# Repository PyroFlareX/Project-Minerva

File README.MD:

# Project Minerva

A custom clamshell handheld computer built around the Raspberry Pi Compute Module 5. Minerva combines a gaming-controller form factor with a full Linux environment: dual displays, cellular connectivity, NFC/RFID, and a security-first immutable OS. Every layer of software — compositor, shell, applications — is purpose-built for controller-style interaction.

> **Device:** Minerva &nbsp;|&nbsp; **OS:** Minerva OS &nbsp;|&nbsp; **Desktop Environment:** Torchform

---

## Screenshots & Hardware

| | |
|---|---|
|  |  |
| Torchform shell — home grid, status bar, dock | CM5 carrier board 3D render |
|  |  |
| Work-in-progress PCB layout (KiCad 9) | DSI/CSI display and camera connectors |

---

## What It Is

Minerva is not a game console. It is a general-purpose handheld Linux computer designed for an unconventional input paradigm — no keyboard, no precise pointer. The form factor is a direct reference to the New Nintendo 3DS (KTR-001, 2014), matching its footprint almost exactly while adding 8mm of thickness for the CM5 module and a 5000mAh battery.

**Core principles:**
- The hardware serves the software vision, not the other way around
- Security is structural — immutable root, hardware key storage, physical kill switches
- Minimize runtime overhead across the entire stack (musl libc, Rust binaries, Slint UI)
- Every UI interaction is achievable with the controller alone — no mouse or keyboard assumed

---

## Repository Structure

```
Project-Minerva/
├── Minerva-Hardware/          # KiCad 9 project — CM5 carrier board
│   ├── Minerva-Carrier.kicad_pcb
│   ├── Minerva-Carrier.kicad_sch
│   ├── CM5_GPIO.kicad_sch
│   ├── CM5_HighSpeed.kicad_sch  # MIPI DSI, USB 3.0, PCIe
│   ├── PCIe-M2.kicad_sch        # M.2 NVMe slot
│   └── Minerva-Carrier.kicad_sym
├── Project-Minerva-OS/        # Rust workspace — OS, compositor, shell
├── Torchform/                 # Rust workspace — Desktop Environment
├── Notes/
│   ├── Images/                # Hardware renders, UI screenshots, PCB photos
│   └── minerva-console-hardware-spec-v3.docx
├── Manual/
│   └── WWAN.md                # Cellular modem setup guide
├── Docs/                      # Component datasheets (EM7565, etc.)
├── rpi-scripts/               # Alpine Linux setup and provisioning scripts
└── CONTEXT.md                 # Full design reference document
```

Enclosure CAD is in OnShape (cloud), project name "Project Minerva". Not stored in this repo.

---

## Hardware

### Physical Design

Clamshell handheld. Two shells connected by a friction hinge — holds the lid at any angle, with a 130–140° stop to protect flex cables.

| Dimension | Value |
|-----------|-------|
| Width | 145 mm |
| Depth (closed) | 82 mm |
| Total height (closed) | 30 mm |
| Shell wall thickness | 2 mm |
| Corner roundedness | 30° fillets |
| Reference device | New Nintendo 3DS (KTR-001) |

The lower shell is divided by a central structural spine: battery on the left (~5000mAh LiPo pouch), mainboard electronics on the right. The 3.5" lower touchscreen spans across both zones above the hinge.

### Compute Module — Raspberry Pi CM5

| Parameter | Value |
|-----------|-------|
| CPU | ARM Cortex-A76 quad-core, up to 2.4GHz |
| GPU | VideoCore VII — OpenGL ES 3.1, Vulkan 1.2 |
| RAM | 8GB LPDDR4X |
| Storage (eMMC) | 32GB — OS partitions only |
| PCIe | Gen 2 ×1 → NVMe SSD |
| USB | 1× USB 3.0 (WWAN modem) + 1× USB 2.0 (USB-C) |
| Display | 2× MIPI DSI |
| WiFi | 802.11ac dual-band |
| Bluetooth | 5.0 |

### Carrier Board (KiCad 9)

Custom 4-layer carrier board. Key design constraints:
- **CM5 connector:** Hirose DF40C-100DS-0.4V (0.4mm pitch)
- **MIPI DSI:** 90Ω differential pairs, length-matched, away from switching regulators
- **USB 3.0:** 90Ω SuperSpeed differential pairs, minimize vias
- **PCIe (NVMe):** 85Ω differential, AC coupling caps on TX pairs
- **RF traces (NFC, WWAN):** 50Ω microstrip with clean ground plane

| Layer | Purpose |
|-------|---------|
| 1 (Top) | Components and signals |
| 2 | Ground plane — unbroken under RF and high-speed |
| 3 | Power planes (3.3V, 1.8V) |
| 4 (Bottom) | Signals, some components |

### Display System

| Display | Size | Resolution | Interface | Touch |
|---------|------|-----------|-----------|-------|
| Upper (primary) | 5.5" | 1920×1080 | MIPI DSI via hinge FPC | No |
| Lower (companion) | 3.5" | 640×480 | MIPI DSI + I2C touch controller | Yes (capacitive) |

The upper screen is the application viewport. The lower screen is contextual — its content changes based on what is focused on the upper screen (virtual keyboard, radial menus, status info, secondary app views). This is architecturally similar to the Nintendo DS / Wii U GamePad, not a simple extended desktop.

### Input System

| Input | Type | Interface |
|-------|------|-----------|
| Left pad | Cirque GlidePoint circular capacitive (35–40mm) | SPI0 direct to CM5 |
| Right stick | Hall effect analog (TLV493D / AS5600) | I2C via input MCU |
| D-pad | 4-way digital | Input MCU GPIO |
| A, B, X, Y | Digital face buttons | Input MCU GPIO |
| L1, R1 | Digital shoulder buttons | Input MCU GPIO |
| L2, R2 | Analog triggers | Input MCU ADC |
| Start / Select | Digital | Input MCU GPIO |
| Lower screen | Capacitive touch | I2C touch controller |

A dedicated input MCU (RP2040 or STM32F0) handles button scanning, debouncing, and ADC. The Cirque trackpad connects directly to CM5 SPI0 via the `cirque_pinnacle` mainline kernel driver.

#### Input Grammar

| Input | Action |
|-------|--------|
| Left pad (Cirque) | Cursor / navigation |
| D-pad | Spatial focus movement between UI elements |
| A | Confirm / select |
| B | Back / cancel |
| L2 (hold) | App radial menu — layer 1 |
| R2 (hold) | App radial menu — layer 2 |
| L2 + R2 (hold) | Global system radial menu |
| Select | Command palette |
| Start | App switcher |
| L1 / R1 | Switch tiles (split-screen mode) |

### Storage

| Storage | Use | Encryption |
|---------|-----|-----------|
| eMMC 32GB (on CM5) | OS only — immutable boot image | dm-verity (read-only root) |
| M.2 2230 NVMe (PCIe ×1) | All user data | LUKS2 AES-256-XTS, key from ATECC608B |

### Connectivity

| Radio | Source | Notes |
|-------|--------|-------|
| WiFi 5 | CM5 onboard | MAC randomization on every association |
| Bluetooth 5.0 | CM5 onboard | BLE + Classic |
| WWAN 5G/LTE | Quectel RM520N-GL or EC25-AF | M.2 B-key, USB 3.0 interface |
| NFC (13.56MHz) | NXP PN7150 (I2C) | MIFARE, ISO 14443, HCE |
| 125kHz RFID | Separate module (EM4100/HID Prox) | On main board |

### Power

- Battery: 5000mAh Li-Po single cell
- Charging: USB Power Delivery (5V/3A or 9V/2A fast charge)
- Fuel gauge: BQ27441 or MAX17048 (coulomb counter)
- PMIC: TPS65219 or similar (3.3V, 1.8V, 1.0V rails)
- Clamshell detection: DRV5023 hall effect sensor → suspend on close, wake on open

### Security Hardware

| Component | Purpose |
|-----------|---------|
| ATECC608B | Hardware secure element — LUKS key derivation, ECDH, HMAC-SHA256, anti-rollback counter |
| Optional: Infineon SLB9670 TPM 2.0 | Measured boot, PCR attestation, key sealing |

**Hardware kill switches** (physical slide switches, software cannot override):
- Microphone power rail
- Camera power rail (future)
- All radios (WiFi + BT + WWAN) simultaneously

### Optional Daughterboard (RF + Biometrics)

Attaches via FPC or pin header — can be omitted from the base build.

| Component | Chip | Notes |
|-----------|------|-------|
| Sub-1GHz RF | TI CC1101 | 300–928MHz, ASK/OOK/FSK — same IC as Flipper Zero |
| Infrared TX/RX | IR LED + TSOP38238 | NEC, RC5, Sony SIRC, LIRC stack |
| Fingerprint | Goodix GT9368 | `libfprint` / `fprintd`, always has PIN fallback |

---

## Software

### Minerva OS

**Base:** Alpine Linux, musl libc, OpenRC init system  
**Rust target:** `aarch64-unknown-linux-musl`

#### Boot Chain

```
Power on
  → U-Boot (signed, eMMC partition 1)
    → Verify Slot A via dm-verity hash tree
      → Success: Mount read-only rootfs + overlayfs (config partition)
        → OpenRC → derive LUKS key via ATECC608B → unlock NVMe
          → Mount ZFS volumes → Launch Torchform
      → Failure: Boot Slot B recovery
```

#### Storage Layout

| eMMC Partition | Purpose |
|----------------|---------|
| 1 — Bootloader | U-Boot, signed, read-only |
| 2 — Slot A | Minerva OS verified image (dm-verity, ~4GB) |
| 3 — Slot B | Recovery OS (minimal, read-only, ~2GB) |
| 4 — Boot config | A/B selector, U-Boot environment |
| 5 — Overlay | Writable overlayfs upper layer for `/etc` |

| NVMe Volume (inside LUKS2) | Mount |
|---------------------------|-------|
| Home | `/home/user` |
| Data | `/data` |
| Logs | `/var/log` |
| Swap | `[swap]` |

ZFS is used on the NVMe for snapshots, checksumming, and compression.

#### System Services

| Service | Purpose |
|---------|---------|
| `torchform-compositor` | Smithay Wayland compositor (two outputs) |
| `torchform-inputd` | uinput virtual gamepad + Cirque axis synthesis |
| `pipewire` | Audio server (replaces PulseAudio) |
| `NetworkManager` | WiFi, cellular, VPN |
| `ModemManager` | WWAN modem |
| `neard` / `nfcd` | NFC daemon |
| `whisper.cpp` | On-device speech-to-text (command palette, text fields) |
| `fprintd` | Fingerprint auth (when daughterboard attached) |

---

### Torchform — Desktop Environment

Torchform is a custom Rust DE built entirely for Minerva's controller input paradigm. No GNOME, KDE, or existing DE is used.

See [Torchform/TORCHFORM.md](Torchform/TORCHFORM.md) for full documentation.

#### Technology Stack

| Layer | Technology |
|-------|-----------|
| UI toolkit | Slint (declarative, Rust-native, CSS-adjacent theming) |
| Compositor | Smithay (Rust Wayland compositor library) |
| Input daemon | Custom `torchform-inputd` (Cirque SPI, USB HID, uinput) |
| Design tokens | `tokens.slint` — single source of truth for all theming |

#### Crate Map

| Crate | Role |
|-------|------|
| `torchform-shell` | Main Slint UI — N3DS chrome, overlays, state machine |
| `torchform-apps` | All 12 app UI components (embeddable or standalone) |
| `torchform-compositor` | Smithay two-output compositor, tiling, input |
| `torchform-inputd` | Cirque SPI, USB HID gamepad, uinput, Unix socket |
| `torchform-actions` | `ShellAction` enum + `InputMap` keybinds (no Slint dep) |
| `torchform-config` | `TorchformConfig` TOML loader + settings schema (no Slint dep) |
| `torchform-settings` | Standalone Settings app |
| `torchform-files` | Standalone File Browser app |
| `torchform-terminal` | Writes themed Alacritty/Kitty config then `exec()`s terminal |
| `torchform-run` | Sets Wayland env vars then `exec()`s any app binary |

#### Shell UI

The shell presents a Nintendo-3DS-style chrome on the upper display:

- **Status bar** (top, 28px) — workspace dots, clock, battery, now-playing, notifications indicator
- **Home screen** — 7-app grid + 5-icon dock + search bar
- **App window** — fullscreen or horizontal split (2 tiles max); no floating windows
- **Quick Settings** — right-slide panel; sliders + toggle tiles
- **Notifications** — left-slide panel; notification list
- **App Switcher** — full-screen card row (Start button)
- **Command Palette** — searchable command list (X button)
- **Radial Menus** — primary action pattern; L2/R2 open layers 1/2, L2+R2 opens global system menu
- **Hint bar** (bottom, 24px) — contextual button hints

The lower companion display shows: virtual keyboard, radial menus, status widgets, app-specific secondary content, or idle status (battery, time, quick toggles).

#### App Suite

All apps are Slint + Rust, designed for controller input (no keyboard/mouse assumptions):

| App | Status |
|-----|--------|
| Settings | Working (schema-driven, sliders/toggles/selects) |
| File Manager | Working (directory navigation, file sizes, icons) |
| Terminal | Working (launches Alacritty or Kitty with themed config) |
| System Monitor | UI ready; backend polling not yet implemented |
| Package Manager | UI ready; backend not yet implemented |
| Log Viewer | UI ready |
| Notes | UI ready |
| Network Manager | UI ready; no backend integration |
| Web Browser | Planned (Servo embedded or Chromium kiosk) |
| Media Player | Planned (mpv backend) |
| Phone / SMS / Email | UI components ready; no backend |
| Camera | Planned (future — hardware not in initial scope) |

**App design constraints** (all apps must follow):
- No dropdown menus — use enumeration pickers (cycle with A/B or D-pad)
- No text fields requiring a physical keyboard — use voice (Whisper.cpp) or lower-screen virtual keyboard
- UI controls limited to: sliders, checkboxes, enumeration pickers
- Every interactive element reachable by D-pad spatial navigation
- Fullscreen layout (1920×1080 upper screen primary viewport)
- Every app defines what it shows on the lower 3.5" screen

#### Quick Start — Desktop Development (No Hardware Required)

```bash
# Build and run the shell emulator (single window with both displays)
cd Torchform
cargo run -p torchform-shell

# Demo modes:
cargo run -p torchform-shell -- --demo radial     # radial menu open
cargo run -p torchform-shell -- --demo switcher   # app switcher open
cargo run -p torchform-shell -- --demo idle       # lower screen idle state

# Two separate windows (mirrors physical layout)
cargo run -p torchform-shell -- --standalone

# Makefile shortcuts:
make run-emulator
make run-standalone
make check          # fast type-check (no hardware libs needed)
make build-all      # full workspace (needs libseat, libinput, libgbm)
```

**Emulator keyboard shortcuts:**

| Key | Action |
|-----|--------|
| Space | Select / go home |
| Enter | Start / app switcher |
| Tab (hold/release) | L2 — radial menu |
| Esc | B — back/cancel |
| A | A — confirm |
| X | Command palette |
| Z | Quick Settings |
| C | Notifications |
| Arrow keys | D-pad |
| I / J / K / L | Analog stick N/W/S/E |

**System dependencies (Debian/Ubuntu):**
```bash
sudo apt-get install \
    libseat-dev libinput-dev libgbm-dev libdrm-dev \
    libudev-dev libxkbcommon-dev libwayland-dev \
    libx11-dev libx11-xcb-dev libevdev-dev \
    pkg-config build-essential
```

---

### Minerva OS — Rust Workspace

See [Project-Minerva-OS/README.md](Project-Minerva-OS/README.md) for full build documentation.

```bash
cd Project-Minerva-OS
make build        # cross-compile all crates for ARM64
make image        # build full disk image
make run          # test in QEMU ARM64
make deploy-bins  # push updated binaries to CM5 over SSH
```

---

## Development Status

| Subsystem | Status |
|-----------|--------|
| Carrier board schematic | In progress |
| Carrier board PCB layout | In progress — diff pair routing active |
| Enclosure CAD (OnShape) | In progress |
| Torchform shell emulator | Working — run `make run-emulator` |
| Radial menu UI | Working |
| Command palette UI | Working |
| App switcher UI | Working (display only) |
| Settings app | Working |
| File manager | Working |
| Input virtualization (`ShellAction` + `InputMap`) | Working |
| Wayland compositor (Winit backend) | Working |
| Wayland compositor (DRM/KMS) | Stub — pending hardware |
| Input daemon (Cirque SPI) | Written — requires CM5 hardware |
| System actions (brightness, volume, WiFi) | UI complete; no backend syscalls |
| App switcher close/switch logic | Not yet implemented |
| Sysmon, Pkgman, Logview backends | Not yet implemented |
| Phone / SMS / Email backends | Not yet implemented |
| Alpine OS image build | In progress |
| LUKS + ATECC608B key derivation | Design complete |

---

## Open Questions

**Hardware:**
1. Cirque trackpad: TM035035 (35mm) vs TM040040 (40mm) — depends on physical fit
2. L2/R2 analog vs digital triggers — analog preferred for gaming, adds ADC complexity
3. Fan vs passive cooling — thermal testing needed with CM5 under load
4. Input MCU: RP2040 vs STM32F0 (RP2040 cheaper + USB HID; STM32F0 has better ADC)
5. Daughterboard connector: FPC vs pin header

**Software:**
6. App sandboxing model: containers (LXC/Podman) vs Wayland-only isolation vs seccomp-bpf vs hybrid
7. Workspace persistence: how `workspace.toml` files are managed and discovered
8. OS update mechanism: how Slot A images are built, signed, and deployed (OTA vs USB flash)
9. Whisper.cpp model size: tiny / base / small (accuracy vs CPU tradeoff on CM5)
10. Lower screen display server: distinct Wayland output vs managed Slint surfaces

---

## Key References

- [CONTEXT.md](CONTEXT.md) — full design reference (physical, hardware, OS, DE)
- [Torchform/TORCHFORM.md](Torchform/TORCHFORM.md) — Torchform DE documentation
- [Torchform/CLAUDE.md](Torchform/CLAUDE.md) — Torchform Claude context (architecture deep-dive)
- [Manual/WWAN.md](Manual/WWAN.md) — Cellular modem setup
- [Docs/](Docs/) — Component datasheets

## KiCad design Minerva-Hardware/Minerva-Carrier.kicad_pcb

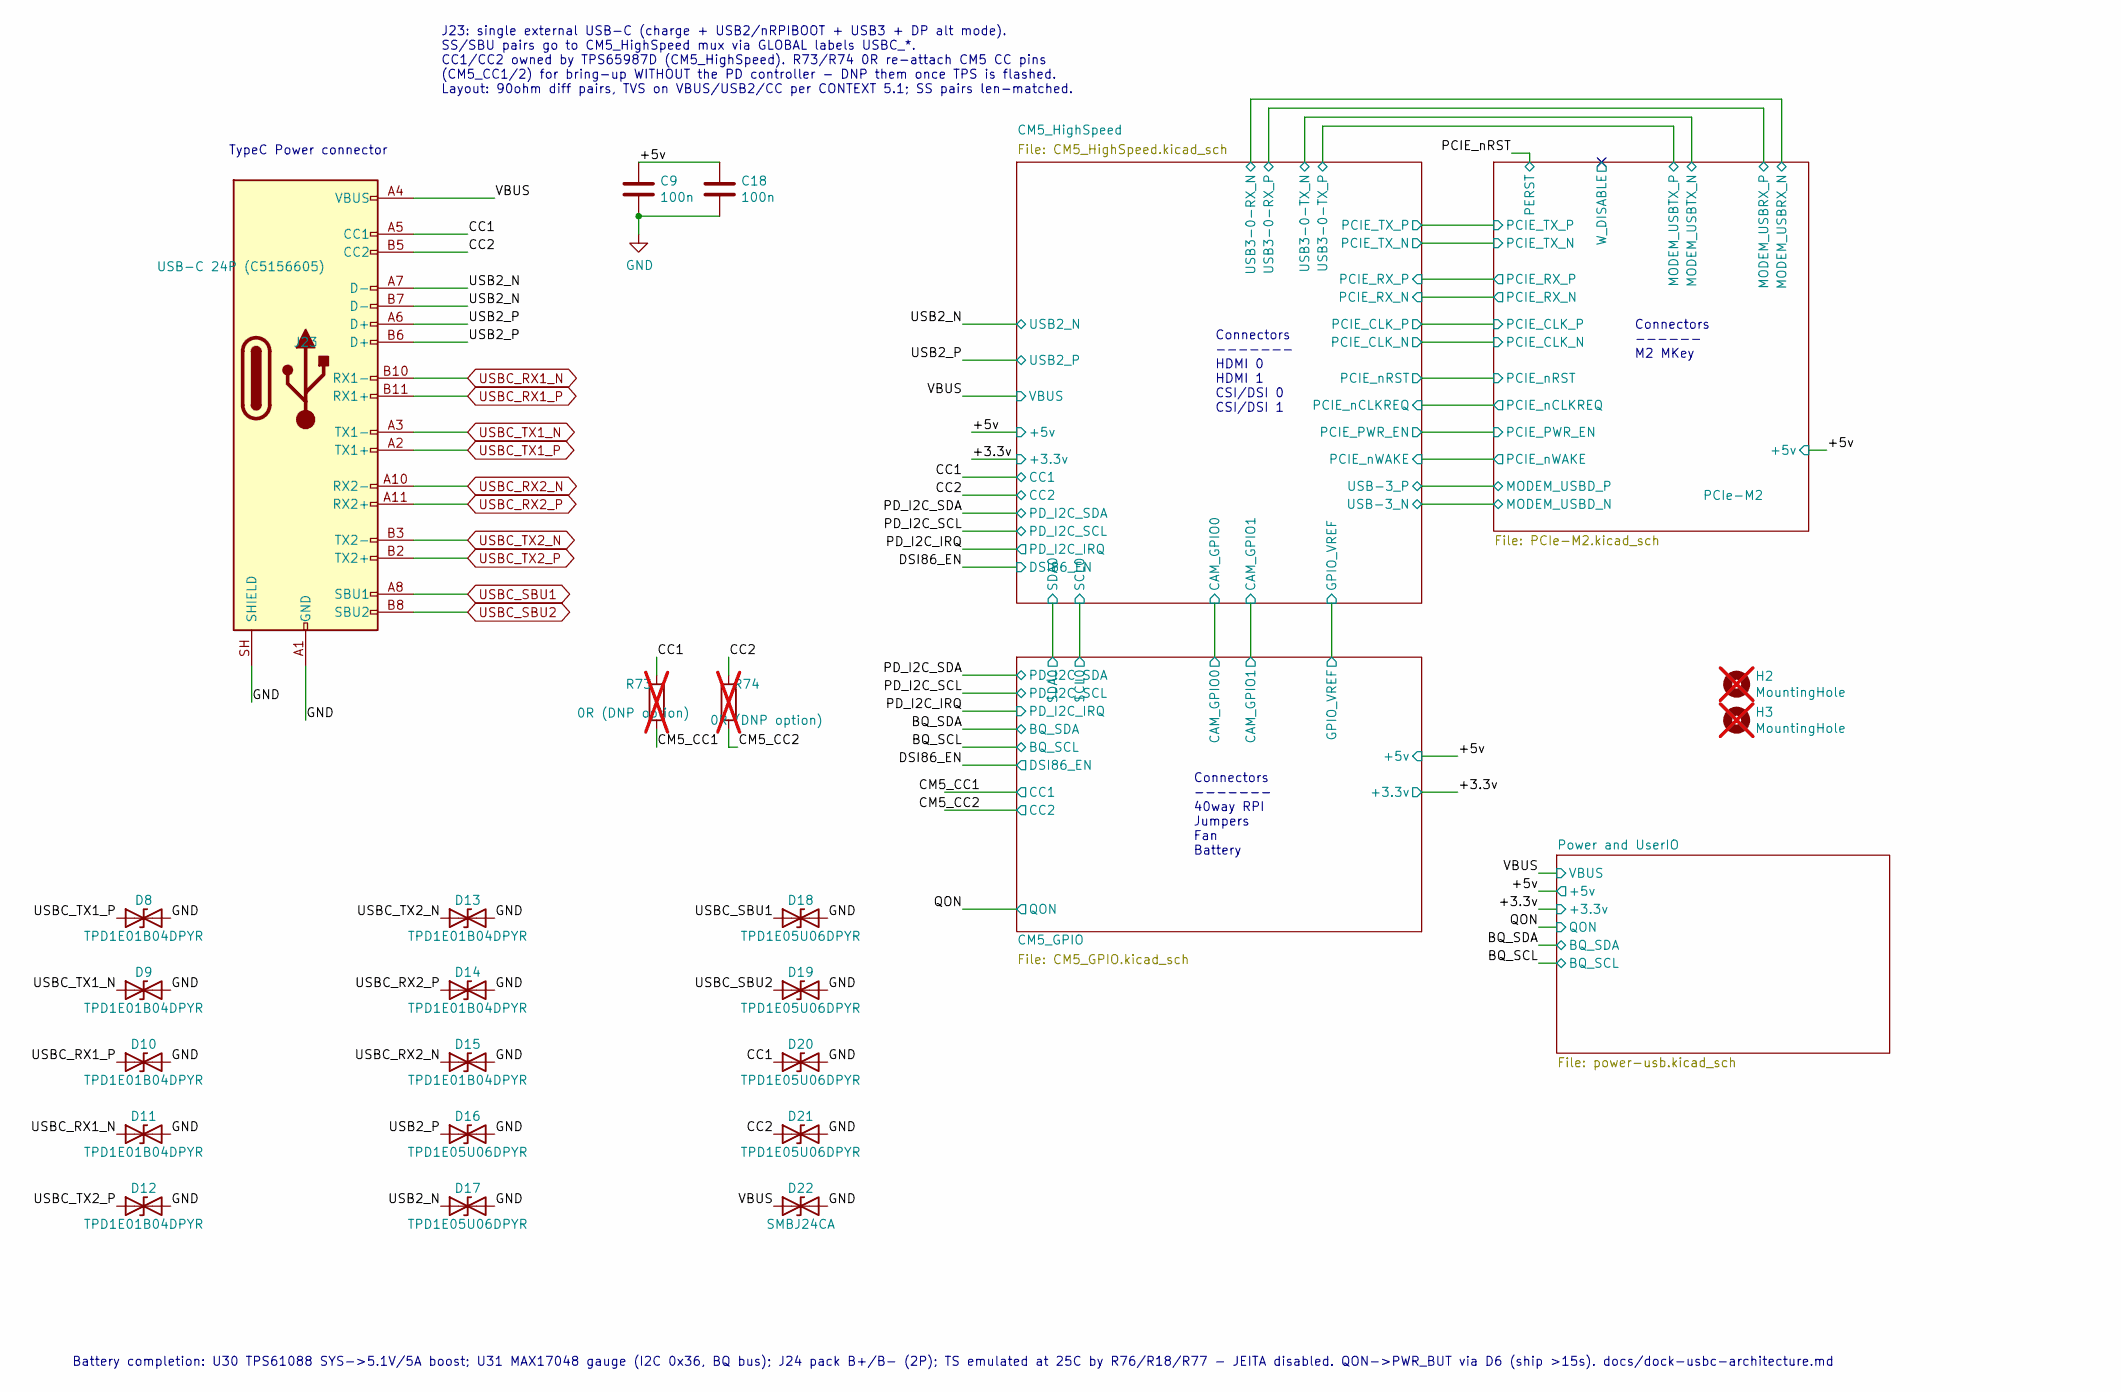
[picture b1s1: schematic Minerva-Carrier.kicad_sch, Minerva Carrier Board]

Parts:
C9, C18: 100n; C_0402_1005Metric; Part Description 0.1uF 10% 16V Ceramic Capacitor X7R 040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
D8, D9, D10, D11, D12, D13, D14, D15: TPD1E01B04DPYR; Texas_DPY0002A_0.6x1mm_P0.65mm; MPN TPD1E01B04DPYR
D16, D17, D18, D19, D20, D21: TPD1E05U06DPYR; Texas_DPY0002A_0.6x1mm_P0.65mm; MPN TPD1E05U06DPYR
D22: SMBJ24CA; D_SMB; MPN SMBJ24CA
H2, H3: MountingHole; MountingHole_2.7mm_M2.5_DIN965; Part Description M2.5 mounting hole; not fitted
J23: USB-C 24P (C5156605); USB_C_Receptacle_Amphenol_12401610E4-2A_CircularHoles; Part Description Full-featured USB-C receptacle: PD sink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
R73, R74: 0R (DNP option); R_0402_1005Metric; MPN RC0402JR-070RL; not fitted

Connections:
/+5v: C9.1, C18.1; also elsewhere on the board
/CC1: D20.1 (A1), J23.A5 (CC1), R73.1; also elsewhere on the board
/CC2: D21.1 (A1), J23.B5 (CC2), R74.1; also elsewhere on the board
/CM5_CC1: R73.2; also elsewhere on the board
/CM5_CC2: R74.2; also elsewhere on the board
/USB2_N: D17.1 (A1), J23.A7 (D-), J23.B7 (D-); also elsewhere on the board
/USB2_P: D16.1 (A1), J23.A6 (D+), J23.B6 (D+); also elsewhere on the board
/VBUS: D22.1 (A1), J23.A4 (VBUS), J23.A9 (VBUS), J23.B4 (VBUS), J23.B9 (VBUS); also elsewhere on the board
GND: C9.2, C18.2, D8.2 (A2), D9.2 (A2), D10.2 (A2), D11.2 (A2), D12.2 (A2), D13.2 (A2), D14.2 (A2), D15.2 (A2), D16.2 (A2), D17.2 (A2), D18.2 (A2), D19.2 (A2), D20.2 (A2), D21.2 (A2), D22.2 (A2), J23.15, J23.16, J23.17, J23.18, J23.A1 (GND), J23.A12 (GND), J23.B1 (GND), J23.B12 (GND), J23.SH (SHIELD); also elsewhere on the board
USBC_RX1_N: D11.1 (A1), J23.B10 (RX1-); also elsewhere on the board
USBC_RX1_P: D10.1 (A1), J23.B11 (RX1+); also elsewhere on the board
USBC_RX2_N: D15.1 (A1), J23.A10 (RX2-); also elsewhere on the board
USBC_RX2_P: D14.1 (A1), J23.A11 (RX2+); also elsewhere on the board
USBC_SBU1: D18.1 (A1), J23.A8 (SBU1); also elsewhere on the board
USBC_SBU2: D19.1 (A1), J23.B8 (SBU2); also elsewhere on the board
USBC_TX1_N: D9.1 (A1), J23.A3 (TX1-); also elsewhere on the board
USBC_TX1_P: D8.1 (A1), J23.A2 (TX1+); also elsewhere on the board
USBC_TX2_N: D13.1 (A1), J23.B3 (TX2-); also elsewhere on the board
USBC_TX2_P: D12.1 (A1), J23.B2 (TX2+); also elsewhere on the board

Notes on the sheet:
Connectors ------- 40way RPI Jumpers Fan Battery
J23: single external USB-C (charge + USB2/nRPIBOOT + USB3 + DP alt mode). SS/SBU pairs go to CM5_HighSpeed mux via GLOBAL labels USBC_*. CC1/CC2 owned by TPS65987D (CM5_HighSpeed). R73/R74 0R re-attach CM5 CC pins (CM5_CC1/2) for bring-up WITHOUT the PD controller - DNP them once TPS is flashed. La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
Connectors ------ M2 MKey
TypeC Power connector
Connectors ------- HDMI 0 HDMI 1 CSI/DSI 0 CSI/DSI 1
Battery completion: U30 TPS61088 SYS->5.1V/5A boost; U31 MAX17048 gauge (I2C 0x36, BQ bus); J24 pack B+/B- (2P); TS emulated at 25C by R76/R18/R77 - JEITA disabled. QON->PWR_BUT via D6 (ship >15s). docs/dock-usbc-architecture.md

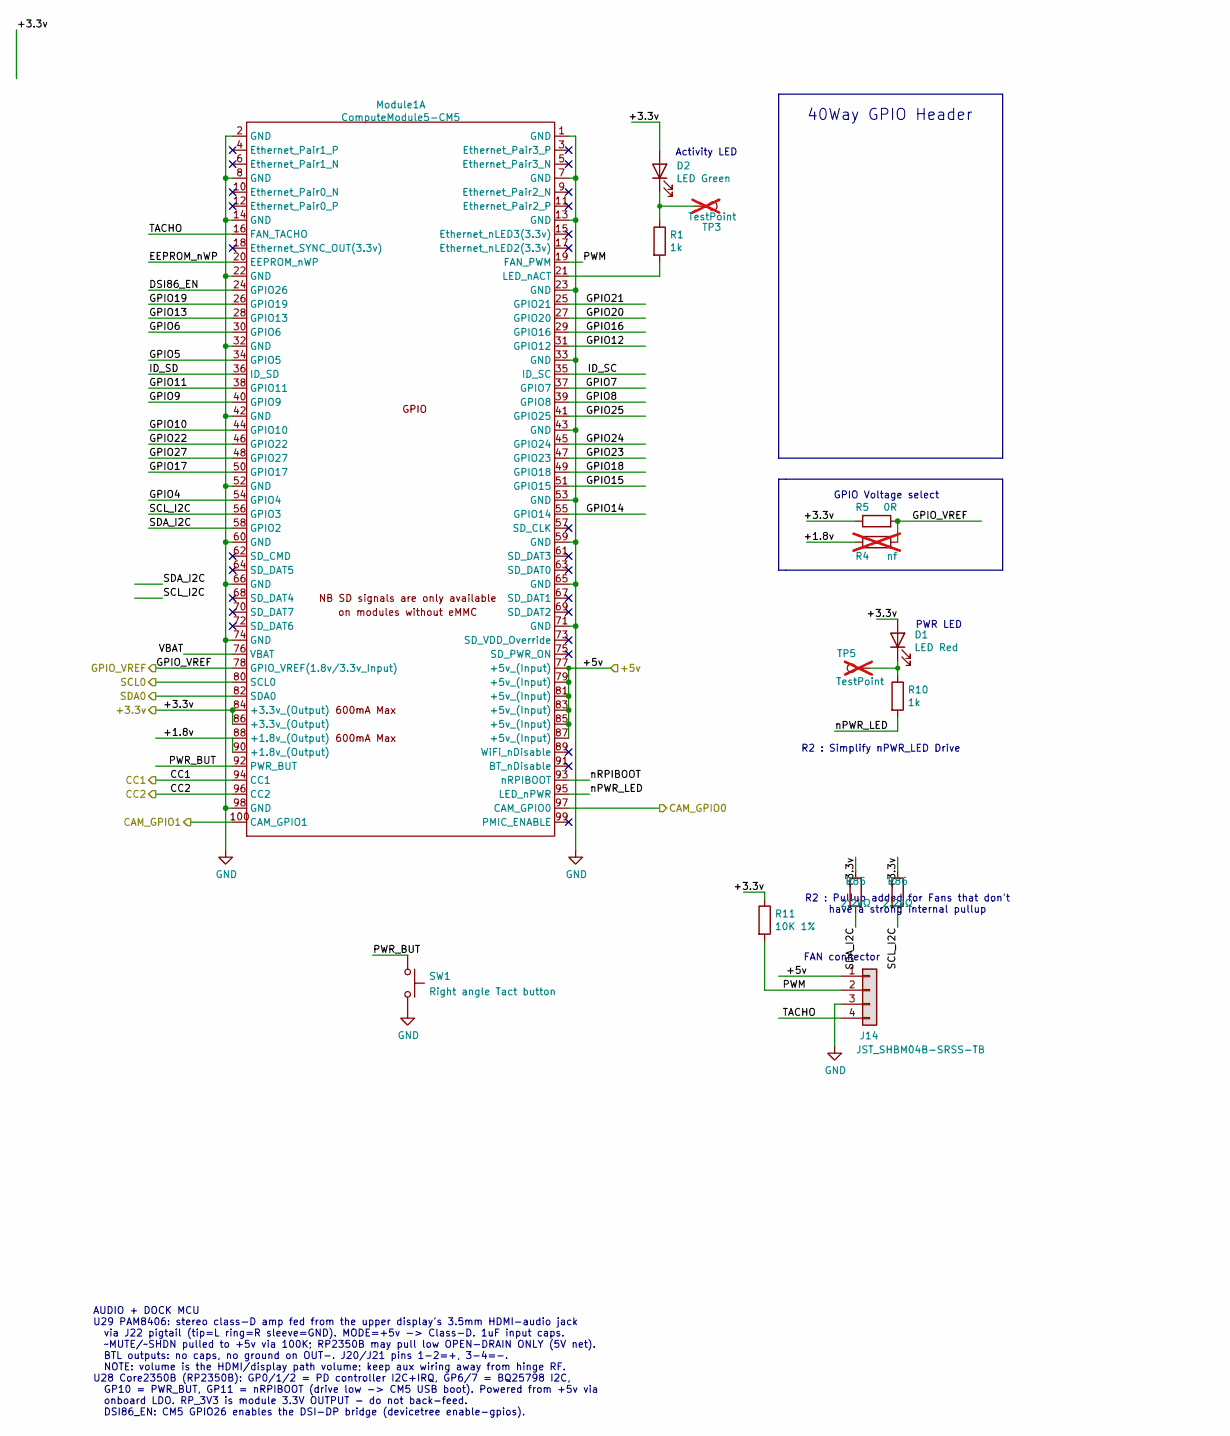
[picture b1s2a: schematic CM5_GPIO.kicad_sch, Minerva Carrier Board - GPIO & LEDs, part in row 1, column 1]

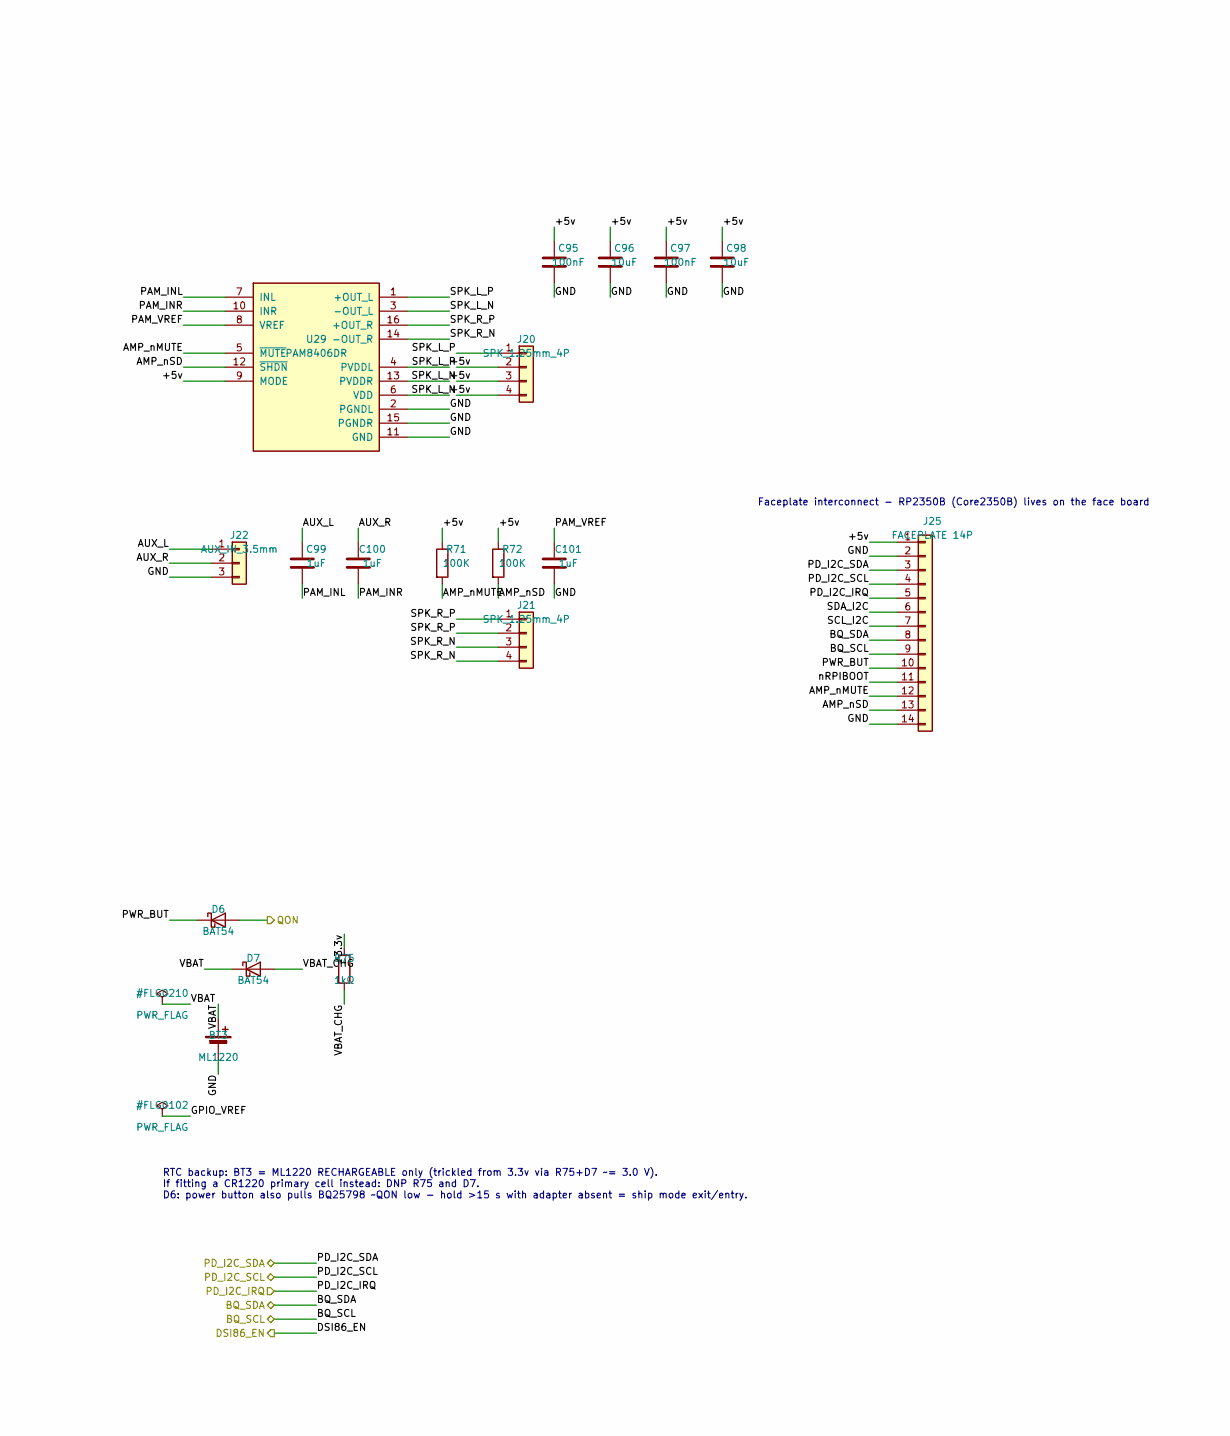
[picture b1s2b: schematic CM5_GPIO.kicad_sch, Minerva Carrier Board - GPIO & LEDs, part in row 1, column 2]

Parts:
BT3: ML1220; BatteryHolder_Keystone_3000_1x12mm; MPN ML-1220
C95, C97: 100nF; C_0402_1005Metric; MPN EMK105B7104KV-F
C96, C98: 10uF; C_0603_1608Metric; MPN CL10A106KP8NNNC
C99, C100, C101: 1uF; C_0402_1005Metric; MPN CC0402KRX5R6BB105
D1: LED Red; LED_0603_1608Metric; Part Description Red 620nm LED Indication - Discrete 2.2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
D2: LED Green; LED_0603_1608Metric; Part Description Green 572nm LED Indication - Discrete 2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
D6, D7: BAT54; D_SOT-23_BAT54_AK; MPN BAT54-7-F
J14: JST_SHBM04B-SRSS-TB; JST_SH_BM04B-SRSS-TB_1x04-1MP_P1.00mm_Vertical; Part Description 4 pin vertical 1mm pitch connector
J20: SPK_1.25mm_4P; Molex_PicoBlade_53398-0471_1x04-1MP_P1.25mm_Vertical; Part Description Left speaker 2030 cavity 8ohm 2W, 1.25m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
J21: SPK_1.25mm_4P; Molex_PicoBlade_53398-0471_1x04-1MP_P1.25mm_Vertical; Part Description Right speaker 2030 cavity 8ohm 2W, 1.25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
J22: AUX_IN_3.5mm; JST_SH_BM03B-SRSS-TB_1x03-1MP_P1.00mm_Vertical; Part Description Line-in pigtail from upper display 3.5m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
J25: FACEPLATE 14P; Molex_PicoBlade_53047-1410_1x14_P1.25mm_Vertical; MPN 53047-1410
Module1: ComputeModule5-CM5; Raspberry-Pi-5-Compute-Module; Part Description 100 Position Connector Receptacle, Cent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
R1, R10: 1k; R_0402_1005Metric; Part Description Resistor 1K M1005 1% 63mW
R4: nf; R_0805_2012Metric_Pad1.20x1.40mm_HandSolder; MPN N/A; not fitted
R5: 0R; R_0805_2012Metric_Pad1.20x1.40mm_HandSolder; Part Description Resistor 0R M2012 5%
R11: 10K 1%; R_0402_1005Metric; Part Description Resistor 10K M1005 1% 63mW
R71, R72: 100K; R_0402_1005Metric; MPN RC0402FR-07100KL
R75: 1kΩ; R_0402_1005Metric; MPN RC0402FR-071KL
R85, R86: 2.2kΩ; R_0402_1005Metric; MPN RT0402FRE072K2L
SW1: Right angle Tact button; SW_Tactile_SPST_Angled_PTS645Vx58-2LFS; Part Description Right angle through hole Tact switch
TP3, TP5: TestPoint; TestPoint_Pad_2.0x2.0mm; Part Description Test point; not fitted
U29: PAM8406DR; SOIC-16_3.9x9.9mm_P1.27mm; Part Description Stereo class-D speaker amp fed from dis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

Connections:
+3.3v: D1.2 (A), D2.2 (A), Module1.84 (+3.3v_(Output)), Module1.86 (+3.3v_(Output)), R5.1, R11.1, R75.1, R85.1, R86.1; also elsewhere on the board
/+5v: C95.1, C96.1, C97.1, C98.1, J14.1, J25.1, Module1.77 (+5v_(Input)), Module1.79 (+5v_(Input)), Module1.81 (+5v_(Input)), Module1.83 (+5v_(Input)), Module1.85 (+5v_(Input)), Module1.87 (+5v_(Input)), R71.1, R72.1, U29.4 (PVDDL), U29.6 (VDD), U29.9 (MODE), U29.13 (PVDDR); also elsewhere on the board
/BQ_SCL: J25.9; also elsewhere on the board
/BQ_SDA: J25.8; also elsewhere on the board
/CM5_CC1: Module1.94 (CC1); also elsewhere on the board
/CM5_CC2: Module1.96 (CC2); also elsewhere on the board
/CM5_GPIO/+1.8v: Module1.88 (+1.8v_(Output)), Module1.90 (+1.8v_(Output)), R4.1
/CM5_GPIO/AMP_nMUTE: J25.12, R71.2, U29.5 (~MUTE)
/CM5_GPIO/AMP_nSD: J25.13, R72.2, U29.12 (~SHDN)
/CM5_GPIO/AUX_L: C99.1, J22.1
/CM5_GPIO/AUX_R: C100.1, J22.2
/CM5_GPIO/CAM_GPIO0: Module1.97 (CAM_GPIO0); also elsewhere on the board
/CM5_GPIO/CAM_GPIO1: Module1.100 (CAM_GPIO1); also elsewhere on the board
/CM5_GPIO/EEPROM_nWP: Module1.20 (EEPROM_nWP)
/CM5_GPIO/GPIO4: Module1.54 (GPIO4)
/CM5_GPIO/GPIO5: Module1.34 (GPIO5)
/CM5_GPIO/GPIO6: Module1.30 (GPIO6)
/CM5_GPIO/GPIO7: Module1.37 (GPIO7)
/CM5_GPIO/GPIO8: Module1.39 (GPIO8)
/CM5_GPIO/GPIO9: Module1.40 (GPIO9)
/CM5_GPIO/GPIO10: Module1.44 (GPIO10)
/CM5_GPIO/GPIO11: Module1.38 (GPIO11)
/CM5_GPIO/GPIO12: Module1.31 (GPIO12)
/CM5_GPIO/GPIO13: Module1.28 (GPIO13)
/CM5_GPIO/GPIO14: Module1.55 (GPIO14)
/CM5_GPIO/GPIO15: Module1.51 (GPIO15)
/CM5_GPIO/GPIO16: Module1.29 (GPIO16)
/CM5_GPIO/GPIO17: Module1.50 (GPIO17)
/CM5_GPIO/GPIO18: Module1.49 (GPIO18)
/CM5_GPIO/GPIO19: Module1.26 (GPIO19)
/CM5_GPIO/GPIO20: Module1.27 (GPIO20)
/CM5_GPIO/GPIO21: Module1.25 (GPIO21)
/CM5_GPIO/GPIO22: Module1.46 (GPIO22)
/CM5_GPIO/GPIO23: Module1.47 (GPIO23)
/CM5_GPIO/GPIO24: Module1.45 (GPIO24)
/CM5_GPIO/GPIO25: Module1.41 (GPIO25)
/CM5_GPIO/GPIO27: Module1.48 (GPIO27)
/CM5_GPIO/GPIO_VREF: Module1.78 (GPIO_VREF(1.8v/3.3v_Input)), R4.2, R5.2; also elsewhere on the board
/CM5_GPIO/ID_SC: Module1.35 (ID_SC)
/CM5_GPIO/ID_SD: Module1.36 (ID_SD)
/CM5_GPIO/PAM_INL: C99.2, U29.7 (INL)
/CM5_GPIO/PAM_INR: C100.2, U29.10 (INR)
/CM5_GPIO/PAM_VREF: C101.1, U29.8 (VREF)
/CM5_GPIO/PWM: J14.2, Module1.19 (FAN_PWM), R11.2
/CM5_GPIO/PWR_BUT: D6.1 (K), J25.10, Module1.92 (PWR_BUT), SW1.1
/CM5_GPIO/SCL_I2C: J25.7, Module1.56 (GPIO3), R86.2
/CM5_GPIO/SDA_I2C: J25.6, Module1.58 (GPIO2), R85.2
/CM5_GPIO/SPK_L_N: J20.3, J20.4, U29.3 (-OUT_L)
/CM5_GPIO/SPK_L_P: J20.1, J20.2, U29.1 (+OUT_L)
/CM5_GPIO/SPK_R_N: J21.3, J21.4, U29.14 (-OUT_R)
/CM5_GPIO/SPK_R_P: J21.1, J21.2, U29.16 (+OUT_R)
/CM5_GPIO/TACHO: J14.4, Module1.16 (FAN_TACHO)
/CM5_GPIO/VBAT: BT3.1 (+), D7.1 (K), Module1.76 (VBAT)
/CM5_GPIO/VBAT_CHG: D7.2 (A), R75.2
/CM5_GPIO/nPWR_LED: Module1.95 (LED_nPWR), R10.2
/CM5_GPIO/nRPIBOOT: J25.11, Module1.93 (nRPIBOOT)
/CM5_HighSpeed/SCL0: Module1.80 (SCL0); also elsewhere on the board
/CM5_HighSpeed/SDA0: Module1.82 (SDA0); also elsewhere on the board
/DSI86_EN: Module1.24 (GPIO26); also elsewhere on the board
/PD_I2C_IRQ: J25.5; also elsewhere on the board
/PD_I2C_SCL: J25.4; also elsewhere on the board
/PD_I2C_SDA: J25.3; also elsewhere on the board
/QON: D6.2 (A); also elsewhere on the board
GND: BT3.2 (-), C95.2, C96.2, C97.2, C98.2, C101.2, J14.3, J22.3, J25.2, J25.14, Module1.1 (GND), Module1.2 (GND), Module1.7 (GND), Module1.8 (GND), Module1.13 (GND), Module1.14 (GND), Module1.22 (GND), Module1.23 (GND), Module1.32 (GND), Module1.33 (GND), Module1.42 (GND), Module1.43 (GND), Module1.52 (GND), Module1.53 (GND), Module1.59 (GND), Module1.60 (GND), Module1.65 (GND), Module1.66 (GND), Module1.71 (GND), Module1.74 (GND), Module1.98 (GND), SW1.2, U29.2 (PGNDL), U29.11 (GND), U29.15 (PGNDR); also elsewhere on the board
unnamed: D1.1 (K), R10.1, TP5.1 (1_1)
unnamed: D2.1 (K), R1.1, TP3.1 (1_1)
unnamed: Module1.21 (LED_nACT), R1.2

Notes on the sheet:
40Way GPIO Header
Activity LED
R2 : Simplify nPWR_LED Drive
RTC backup: BT3 = ML1220 RECHARGEABLE only (trickled from 3.3v via R75+D7 ~= 3.0 V). If fitting a CR1220 primary cell instead: DNP R75 and D7. D6: power button also pulls BQ25798 ~QON low - hold >15 s with adapter absent = ship mode exit/entry.
FAN connector
GPIO Voltage select
R2 : Pullup added for Fans that don't have a strong internal pullup
Faceplate interconnect - RP2350B (Core2350B) lives on the face board
AUDIO + DOCK MCU U29 PAM8406: stereo class-D amp fed from the upper display's 3.5mm HDMI-audio jack via J22 pigtail (tip=L ring=R sleeve=GND). MODE=+5v -> Class-D. 1uF input caps. ~MUTE/~SHDN pulled to +5v via 100K; RP2350B may pull low OPEN-DRAIN ONLY (5V net). BTL outputs: no caps, no ground on O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
PWR LED

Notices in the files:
Minerva Hardware/CM5_GPIO.kicad_sch:
Copyright © 2024 Raspberry Pi Ltd.
